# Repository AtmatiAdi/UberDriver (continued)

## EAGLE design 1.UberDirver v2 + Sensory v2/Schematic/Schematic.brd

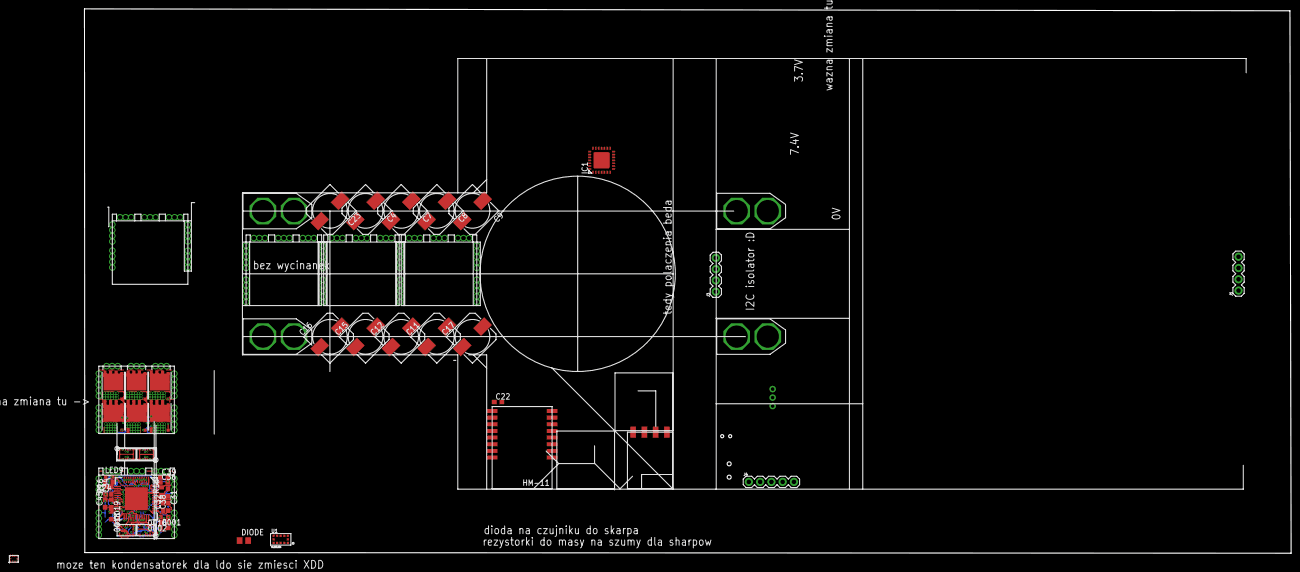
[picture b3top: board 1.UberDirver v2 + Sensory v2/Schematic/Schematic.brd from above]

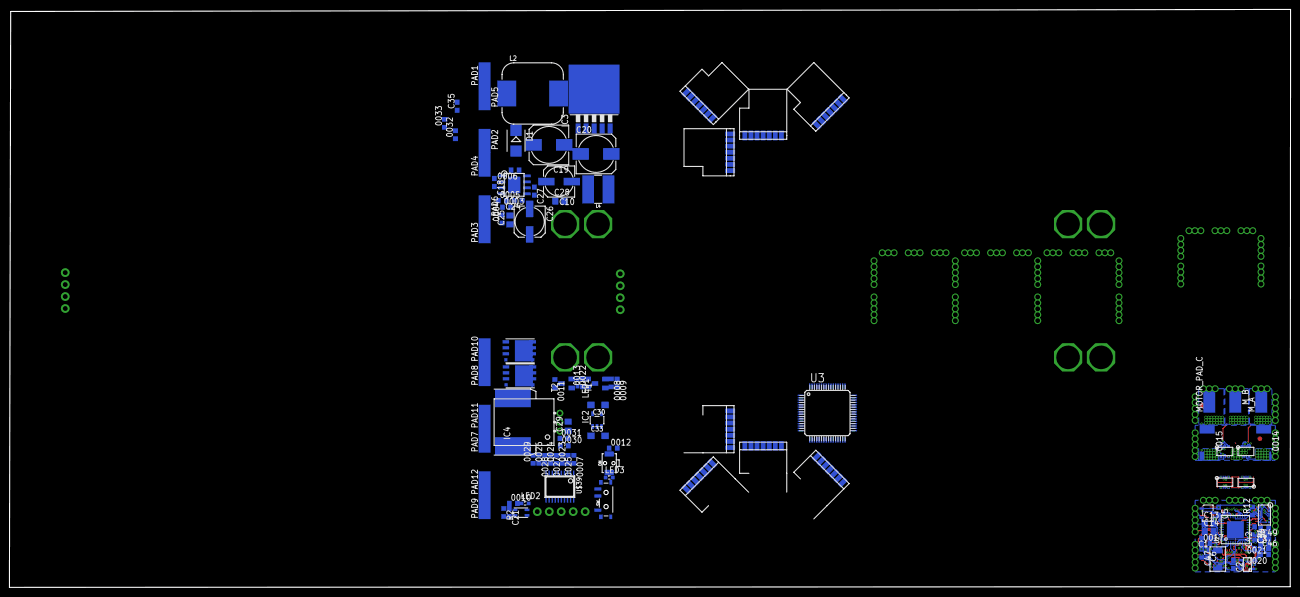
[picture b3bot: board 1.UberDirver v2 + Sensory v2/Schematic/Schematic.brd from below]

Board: 4 copper layers, 271.8 x 122.6 mm, 159 parts (108 on the bottom side), 137 nets.

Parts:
0001, 0016, 0018, 0020: 34.8kR; R0603
0002, 0017, 0019, 0021: 4.99kR; R0603
0003, 0010, 0012, 0013, 0030, 0031: 10k; R0603
0004: 26.1k; R0603
0005: 6.8k; R0603
0006, 0007, 0008, 0011, 0022, 0023, 0025, 0027, 0028: 100k; R0603
0009: 1k; R0603
0014, 0015: 5mohm; R2512
0024: 300k; R0603
0026: 500k; R0603
0029: 700k; R0603
0032, 0033: ?; R0603
C1, C2: 22pF; C0603
C3, C5, C22, C27: 100nF; C0603
C4, C7, C8, C9, C11, C12, C15, C16, C17, C19, C20, C23: 153CLV-0810
C6, C45, C46, C47, C49: 0.1uf; C0603
C10, C26: 10uF; 153CLV-0605
C13, C14: 4.7uF; C0805
C18, C21: 10nF; C0603
C24: 3.9nF; C0603
C25: 22uF; C0805
C28, C29: 10uF; C0805
C30: 10uF/10V; SMC_A
C31, C32: 0.047uF; C0603
C33: 10uf/10V; SMC_A
C34, C36, C38, C39: 1uF; C0603
C35: C0603
C42, C44: 1000pF; C0603
D1: SMB
DIODE: R0805
IC1: MCP23017ML; QFN28-ML_6X6MM
IC2: TPS70933DBV; SOT23-5
IC3: LM2596S; TO263-5
IC4: ACS758ECB-200B-PFF-T; CB-PFF
J1, J3: 1X04
J4: 1X05
L2: CDRH127/LD
L4: 100; SRN6045
LED1, LED2, LED3, LED9: Red; SML0603
MOTOR_PAD_C: SMD2,54-5,08
M_A: SMD2,54-5,08
M_B: SMD2,54-5,08
ON: Button; TACTILE_SWITCH_SMD_RIGHT_ANGLE
PAD1, PAD2, PAD3, PAD4, PAD5, PAD6, PAD7, PAD8, PAD9, PAD10, PAD11, PAD12: SMD2,54-5,08
R1: 180nH; R0603
R2: 100k; R0603
R12, R24: 10k; R0603
R13: 100R; R0603
R16: 100K; R0603
SW: SWITCH_SPST_SMD_A
T1, T2: SOT23-BEC
U1: VL53L0X; LGA12_ST
U2: STM32F10XTXU6HS; VFQFPN36-HS
U3: STM32F10XRXT6; TQFP64
U$1, U$2, U$4, U$5, U$9: MOLEG_REC_8X0.4MM; REC
U$3, U$6, U$7, U$8: MOLEX_PLUG_8X0.4MM; PLUG
U$10: OSC_8MHZ; SMD_MINI
U$11: TLV760XX; SOT-23-3
U$12, U$13, U$22, U$23, U$24, U$25, U$26, U$28: CSD17573Q5B; Q5B
U$14, U$15, U$16, U$18: TOF+SHARP; TOF+SHARP_V1
U$17, U$36, U$37, U$38: XT60
U$19, U$20, U$27, U$29: TOF-SHARP; TOF+SHARP_V2
U$21: DRV8305; S-PQFP-G48
U$30: SUPER_DUPER_GUZICZEK
U$31: TPD4E001; SOT-23
U$32: IR_SW
U$33: TLA2024; X2QFN
U$34: HM-11
U$35: MP2307; SOIC8N
U$39: STM32F030F4; TSSOP20

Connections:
3.7V: 0023.2, PAD9.1, PAD12.1
3V3: 0004.1, C22.2, C25.1, C26.+, J1.3, L4.2, U$32.VCC, U$34.VCC
3V3_L0: 0012.1, C33.+, IC2.5, J4.1, R2.1, U$39.5, U$39.16
5V: 0032.1, C20.+, C29.1, C35.2, IC4.1, J1.4, L2.2, U$14.5V, U$15.5V, U$16.5V, U$18.5V, U$19.5V, U$20.5V, U$27.5V, U$29.5V
7.4V+: 0024.2, C30.+, IC2.1, IC4.IP-, PAD7.1, PAD11.1
7.4V-: IC4.IP+, PAD3.1, PAD6.1
11.1V: 0026.2, PAD1.1, PAD5.1
14.8V: 0029.2, PAD2.1, PAD4.1
+3V3: C5.1, C39.1, C49.1, R1.1, R12.2, R16.1, U2.1, U2.19, U2.27, U$11.1, U$31.5
A3.7: 0007.2, 0023.1, U$39.6
A7.4: 0024.1, 0025.2, U$39.7
A11.1: 0026.1, 0027.2, U$39.8
A14.8: 0028.2, 0029.1, U$39.9
ACURR: 0030.1, 0031.1, U$39.10
BAT-: 0007.1, 0008.1, 0010.1, 0011.2, 0025.1, 0027.1, 0028.1, 0030.2, C21.1, C30.-, C33.-, IC2.2, J4.3, LED3.C, PAD8.1, PAD10.1, T1.E, U$12.S1, U$12.S2, U$12.S3, U$13.S1, U$13.S2, U$13.S3, U$30.T1, U$30.T2, U$39.1, U$39.15
BS: C18.1, U$35.1
BUTTON_L0: LED3.A, ON.1, U$39.13
COMP: C24.1, U$35.6
CURR: 0031.2, IC4.3
EN: 0006.1, U$35.7
ENGATE: U2.24, U$21.1-EN_GATE
FB: 0003.2, 0004.2, U$35.5
GH_ABOT_3: U$9.POWER_2, U$21.36-GH_A
GH_ATOP_2: U$3.POWER_1, U$24.G
GH_BBOT_3: U$4.POWER_4, U$21.29-GH_B
GH_BTOP_2: U$6.POWER_2, U$22.G
GH_CBOT_3: U$4.POWER_3, U$21.28_GH_C
GH_CTOP_1: U$6.POWER_1, U$26.G
GL_ABOT_3: U$9.POWER_3, U$21.33-GL_A
GL_ATOP_2: U$3.POWER_4, U$25.G
GL_BBOT_3: U$4.POWER_2, U$21.32-GL_B
GL_BTOP_2: U$6.POWER_4, U$23.G
GL_CBOT_3: U$4.POWER_1, U$21.25-GL_C
GL_CTOP_1: U$6.POWER_3, U$28.G
GND: 0002.1, 0003.1, 0005.1, 0014.1, 0015.1, 0017.1, 0019.1, 0021.1, 0033.2, C1.2, C2.1, C3.1, C4.-, C5.2, C6.2, C7.-, C8.-, C9.-, C10.-, C11.-, C12.-, C13.2, C15.-, C16.-, C17.-, C19.-, C20.-, C22.1, C23.-, C25.2, C26.-, C27.2, C28.2, C29.2, C34.2, C36.2, C38.2, C39.2, C45.2, C46.2, C47.2, C49.2, D1.A, IC3.3, IC4.2, LED1.C, R24.1, U1.3, U1.4, U1.6, U1.12, U2.5, U2.18, U2.26, U2.35, U2.36, U$1.PAD_1, U$1.PAD_2, U$1.PAD_3, U$1.PAD_4, U$2.PAD_1, U$2.PAD_2, U$2.PAD_3, U$2.PAD_4, U$2.POWER_1, U$3.POWER_3, U$3.SIGNAL_3, U$4.PAD_1, U$4.PAD_2, U$4.PAD_3, U$4.PAD_4, U$5.PAD_1, U$5.PAD_2, U$5.PAD_3, U$5.PAD_4, U$5.POWER_4, U$8.POWER_2, U$9.PAD_1, U$9.PAD_2, U$9.PAD_3, U$9.PAD_4, U$9.POWER_4, U$11.3, U$12.D1, U$12.D2, U$12.D3, U$12.D4, U$12.D5, U$13.D1, U$13.D2, U$13.D3, U$13.D4, U$13.D5, U$14.GND\, U$15.GND\, U$16.GND\, U$17.-, U$18.GND\, U$19.GND\, U$20.GND\, U$21.9-NSCS, U$21.14-GND1, U$21.21-SN2, U$21.22-SP2, U$21.45-GND2, U$21.POWERPAD, U$23.S1, U$23.S2, U$23.S3, U$27.GND\, U$29.GND\, U$31.2, U$32.GND, U$34.GND, U$35.4, U$35.PAD, U$36.-, U$37.-, U$38.-
INH_A: U2.29, U$21.2-INHA
INH_B: U2.13, U$21.4-INHB
INH_C: U2.21, U$21.6-INHC
INL_A: U2.9, U$21.3-INLA
INL_B: U2.14, U$21.5-INLB
INL_C: U2.20, U$21.7-INLC
INPUT: U2.15, U$2.POWER_3
KILL: IC1.22, U$32.KILL
LED: LED9.A, U2.22, U$2.POWER_4
LED_L0: LED2.A, U$39.12
MOSFET: 0009.2, U$39.14
unnamed: 0032.2, 0033.1, C35.1, IC3.4
unnamed: U$5.POWER_3, U$8.POWER_1
unnamed: U$5.SIGNAL_3, U$8.SIGNAL_1
unnamed: U$5.SIGNAL_4, U$8.SIGNAL_2
unnamed: 0008.2, 0009.1, T1.B
unnamed: U$1.POWER_3, U$7.POWER_1
unnamed: U$1.SIGNAL_3, U$7.SIGNAL_1
unnamed: U$1.SIGNAL_4, U$7.SIGNAL_2
unnamed: C36.1, U$21.46-DVDD
unnamed: U$1.POWER_4, U$7.POWER_2
unnamed: C34.1, U$21.15-AVDD
unnamed: C38.1, U$21.37-VCP_LSD
unnamed: C31.2, U$21.42-CP1L
unnamed: U$5.POWER_1, U$8.POWER_3
unnamed: C31.1, U$21.43-CP1H
unnamed: U$5.SIGNAL_1, U$8.SIGNAL_3
unnamed: U$5.SIGNAL_2, U$8.SIGNAL_4
unnamed: U$5.POWER_2, U$8.POWER_4
unnamed: C32.2, U$21.40-CP2L
unnamed: C32.1, U$21.39-CP2H
unnamed: R13.1, U$21.44-VDRAIN
unnamed: C14.2, U$21.38-VCPH
unnamed: C1.1, U2.2, U$10.2
unnamed: U$1.POWER_1, U$7.POWER_3
unnamed: U$1.SIGNAL_1, U$7.SIGNAL_3
unnamed: U$1.SIGNAL_2, U$7.SIGNAL_4
unnamed: U$1.POWER_2, U$7.POWER_4
unnamed: 0022.1, T1.C, T2.B
unnamed: 0005.2, C24.2
unnamed: C3.2, R1.2, U2.6
unnamed: 0010.2, LED2.C
unnamed: C2.2, U2.3, U$10.1
unnamed: 0012.2, ON.2
unnamed: LED9.C, R24.2
unnamed: 0013.1, LED1.A
unnamed: 0011.1, T2.C, U$12.G
NFAULT: R12.1, U2.23, U$21.8-NFAULT
NRST: R16.2, U2.4, U$2.POWER_2
NRST_L0: C21.2, J4.5, R2.2, U$30.T3, U$30.T4, U$39.4
OUT: D1.C, IC3.2, L2.1
SAFE_SW: SW.1, T2.E
SCL: U2.33, U$2.SIGNAL_3
SCLK: U2.30, U$21.12-SCLK
SCL_L: U3.58, U$14.SCL, U$15.SCL, U$16.SCL, U$18.SCL
SCL_L0: J1.1, U$39.17
SCL_R: U3.29, U$19.SCL, U$20.SCL, U$27.SCL, U$29.SCL
SDA: U2.34, U$2.SIGNAL_4
SDA_L: U3.59, U$14.SDA, U$15.SDA, U$16.SDA, U$18.SDA
SDA_L0: J1.2, U$39.18
SDA_R: U3.30, U$19.SDA, U$20.SDA, U$27.SDA, U$29.SDA
SDI: U2.32, U$21.10-SDI
SDO: U2.31, U$21.11-SDO
SHARP_1: IC1.17, U$14.SHARP
SHARP_2: IC1.18, U$15.SHARP
SHARP_3: IC1.19, U$16.SHARP
SHARP_4: IC1.20, U$18.SHARP
SH_ABOT_3: 0018.2, U$9.SIGNAL_1, U$21.35-SH_A
SH_ATOP_2: M_A.1, U$3.SIGNAL_2, U$24.S1, U$24.S2, U$24.S3, U$25.D1, U$25.D2, U$25.D3, U$25.D4, U$25.D5
SH_BBOT_3: 0020.2, U$9.SIGNAL_2, U$21.30-SH_B
SH_BTOP_2: M_B.1, U$3.SIGNAL_1, U$22.S1, U$22.S2, U$22.S3, U$23.D1, U$23.D2, U$23.D3, U$23.D4, U$23.D5
SH_CBOT_3: 0016.2, U$4.SIGNAL_4, U$21.27-SH_C
SH_CTOP_1: MOTOR_PAD_C.1, U$6.SIGNAL_2, U$26.S1, U$26.S2, U$26.S3, U$28.D1, U$28.D2, U$28.D3, U$28.D4, U$28.D5
SL_ABOT_3: C42.1, U$9.SIGNAL_3, U$21.23-SN1, U$21.34-SL_A
SL_ATOP_2: 0014.2, U$3.SIGNAL_4, U$25.S1, U$25.S2, U$25.S3
SL_BOT_3: U$9.SIGNAL_4, U$21.31-SL_B
SL_CTOP_1: 0015.2, U$6.SIGNAL_3, U$28.S1, U$28.S2, U$28.S3
SL_C_2<2: C44.1, U$4.SIGNAL_1, U$21.19-SN3, U$21.26-SL_C
SO1: U2.16, U$21.16-SO1
SO3: U2.12, U$21.18-SO3
SP_ABOT_3: C42.2, U$4.SIGNAL_2, U$21.24-SP1
SP_CBOT_3: C44.2, U$4.SIGNAL_3, U$21.20-SP3
SS: C27.1, U$35.8
START: IC1.21, U$32.START
SW: C18.2, L4.1, U$35.3
SWCLK: U2.28, U$2.SIGNAL_2
SWCLK_L0: J4.2, U$39.20
SWDIO: U2.25, U$2.SIGNAL_1
SWDIO_L0: J4.4, U$39.19
VA: 0018.1, 0019.2, C45.1, U2.7, U$31.1
VB: 0020.1, 0021.2, C46.1, U2.8, U$31.3
VC: 0016.1, 0017.2, C47.1, U2.10, U$31.4
VIN: 0006.2, 0013.2, 0022.2, C4.+, C7.+, C8.+, C9.+, C10.+, C11.+, C12.+, C15.+, C16.+, C17.+, C23.+, C28.1, SW.2, U$17.+, U$35.2, U$36.+, U$37.+, U$38.+
VIN1: C19.+, IC3.1
VMOTOR: 0001.2, C13.1, C14.1, R13.2, U$9.POWER_1, U$11.2, U$21.41-PVDD
VMOTOR_TOP: U$3.POWER_2, U$22.D1, U$22.D2, U$22.D3, U$22.D4, U$22.D5, U$24.D1, U$24.D2, U$24.D3, U$24.D4, U$24.D5, U$26.D1, U$26.D2, U$26.D3, U$26.D4, U$26.D5
VV: 0001.1, 0002.2, C6.1, U2.11, U$31.6
WAKE: U2.17, U$21.47-WAKE
XSHUT_1: IC1.25, U$14.XSHUT
XSHUT_2: IC1.26, U$15.XSHUT
XSHUT_3: IC1.27, U$16.XSHUT
XSHUT_4: IC1.28, U$18.XSHUT

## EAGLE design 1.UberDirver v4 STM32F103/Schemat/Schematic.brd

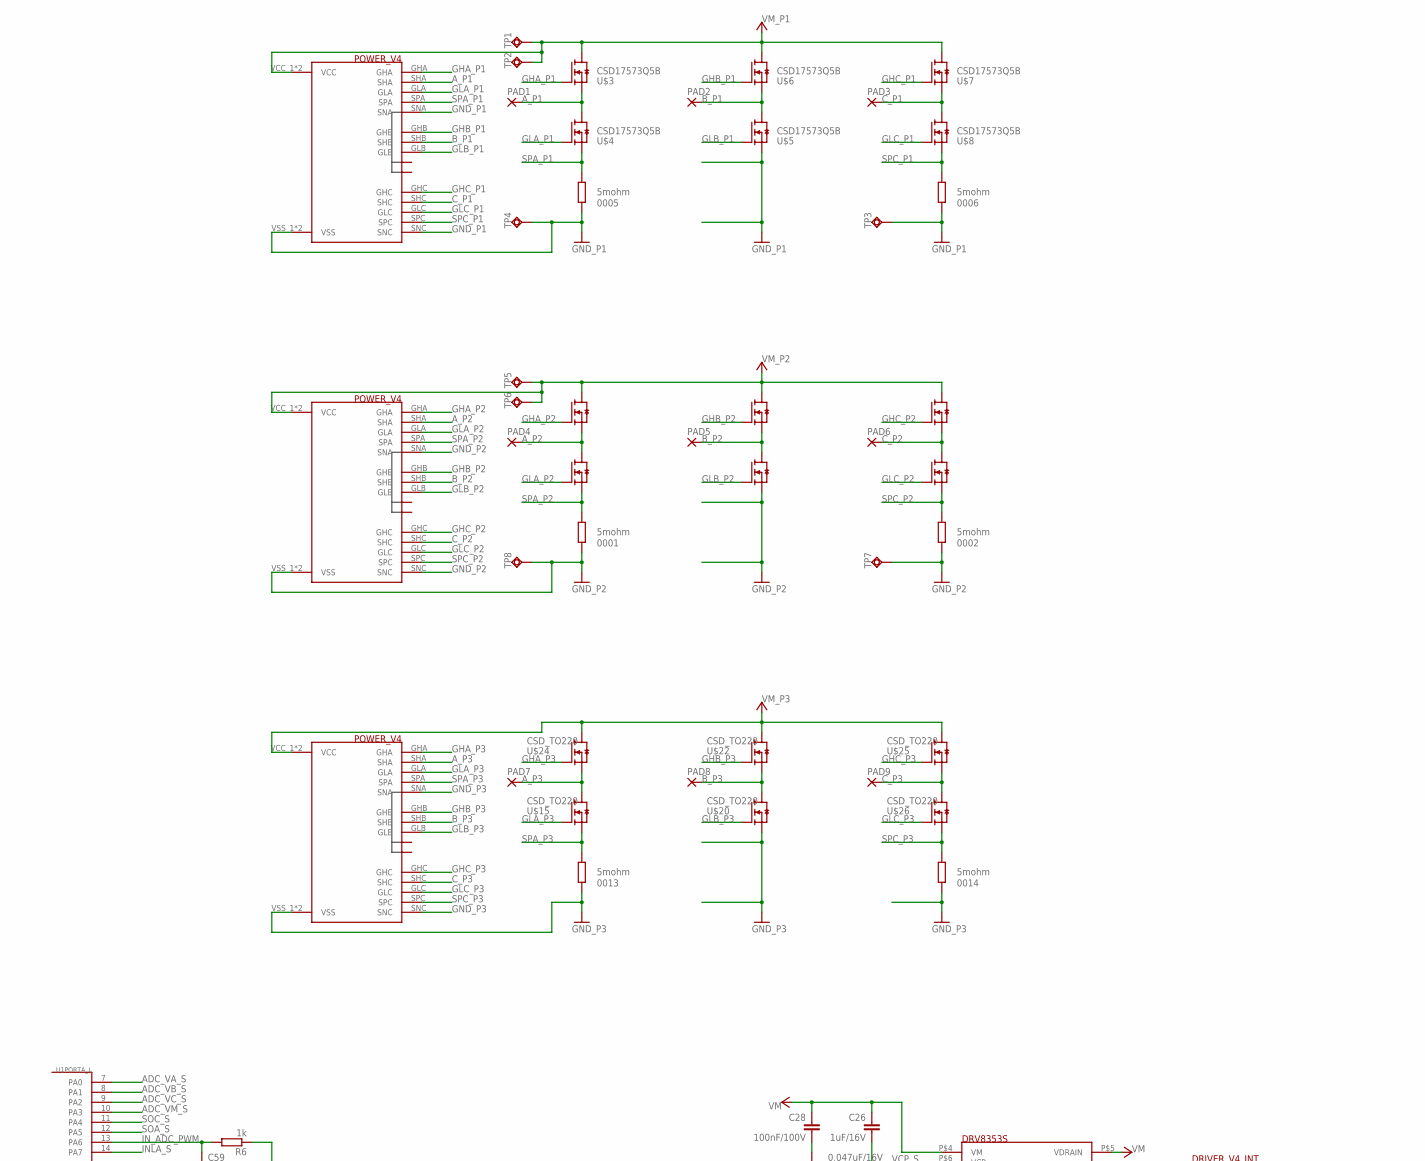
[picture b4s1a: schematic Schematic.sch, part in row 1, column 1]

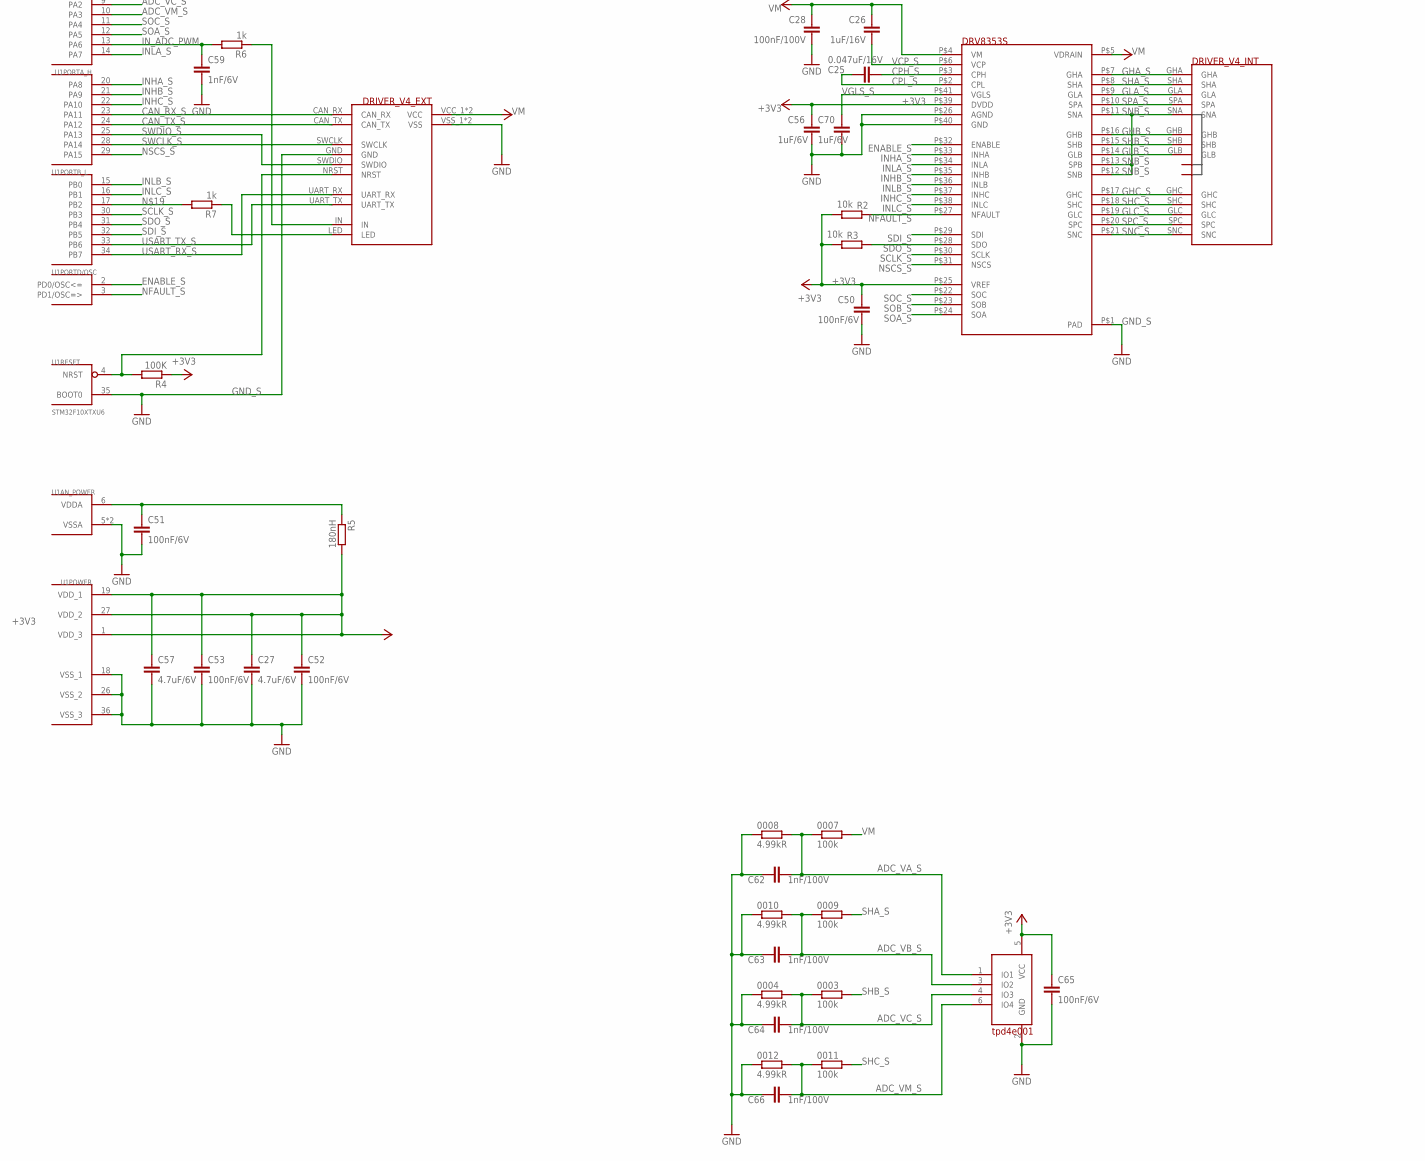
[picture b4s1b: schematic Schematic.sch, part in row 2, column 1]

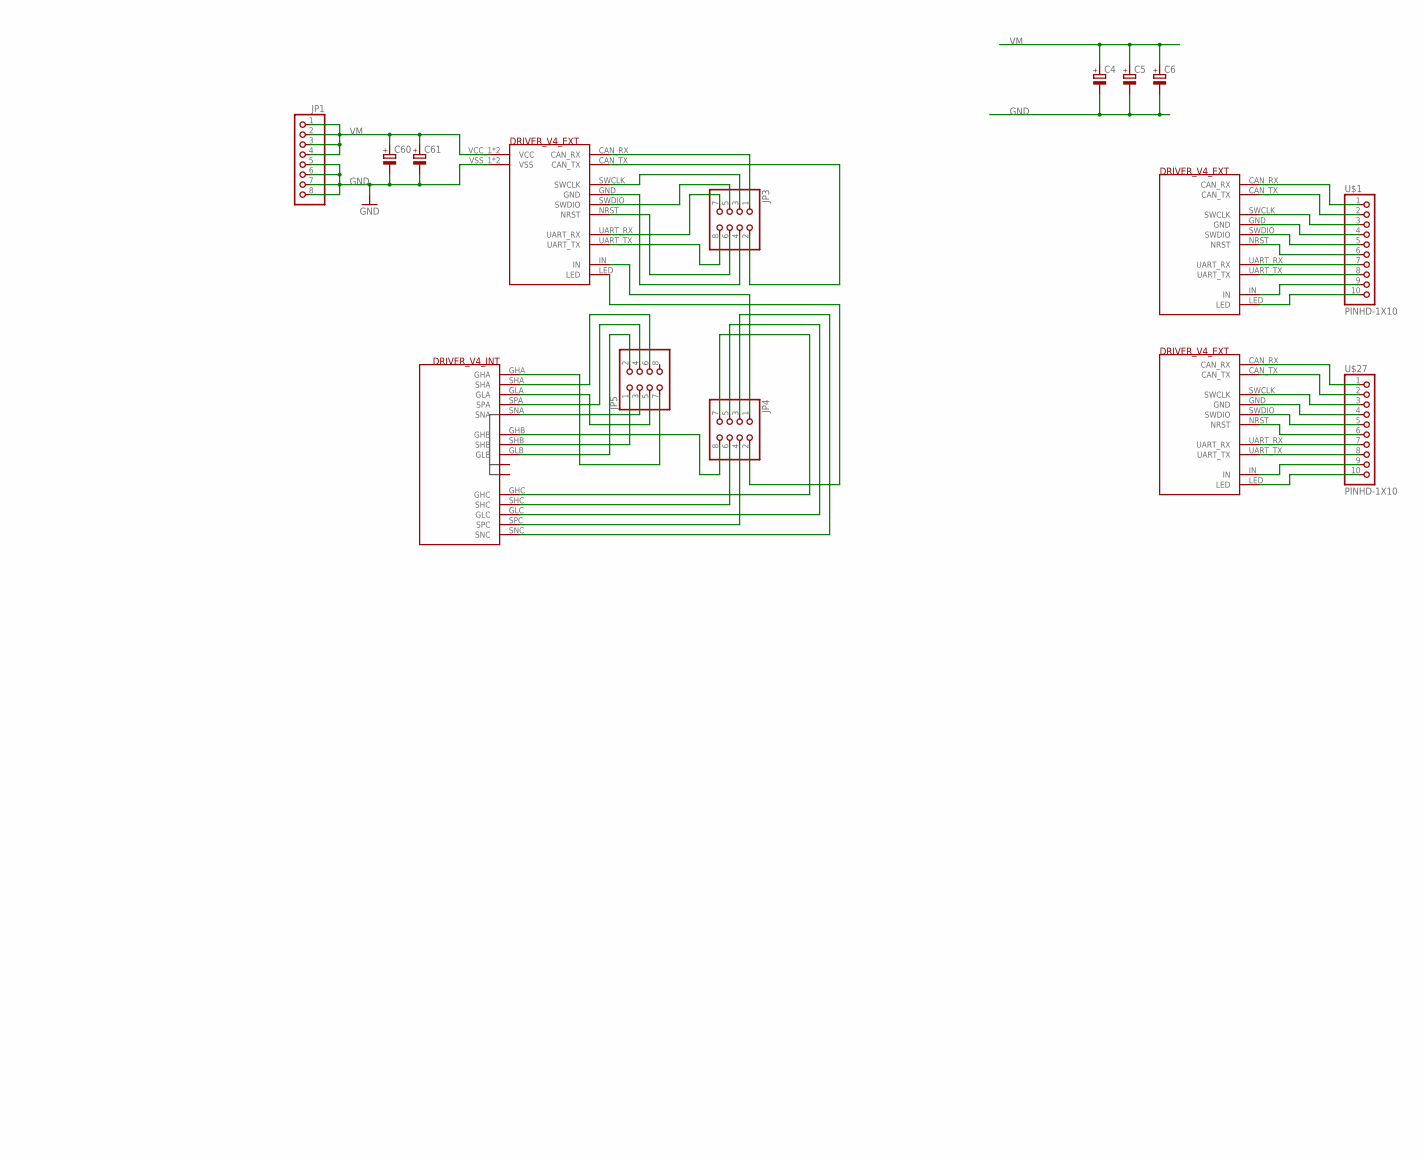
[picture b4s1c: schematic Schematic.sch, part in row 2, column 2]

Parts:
0001, 0002, 0005, 0006, 0013, 0014: 5mohm; R2512
0003, 0007, 0009, 0011: 100k; R0402
0004, 0008, 0010, 0012: 4.99kR; R0402
C4, C5, C6, C60, C61: CPOL-EUE3.5-10; E3,5-10
C25: 0.047uF/16V; R0402
C26: 1uF/16V; R0402
C27, C57: 4.7uF/6V; R0402
C28: 100nF/100V; R0402
C50, C51, C52, C53, C65: 100nF/6V; R0402
C56, C70: 1uF/6V; R0402
C59: 1nF/6V; R0402
C62, C63, C64, C66: 1nF/100V; R0402
JP1: PINHD-1X8BIG; 1X08-BIG
JP3, JP4, JP5: PINHD-2X4; 2X04
PAD1, PAD2, PAD3, PAD4, PAD5, PAD6, PAD7, PAD8, PAD9: SMD5; SMD2,54-5,08
R2, R3: 10k; R0402
R4: 100K; R0402
R5: 180nH; R0402
R6, R7: 1k; R0402
TP1, TP2, TP3, TP4, TP5, TP6, TP7, TP8: TPSQTP20SQ; TP20SQ
U1: STM32F10XTXU6; VFQFPN36
U$1, U$27: PINHD-1X10; 1X10-BIG
U$2, U$23: UBER_V4_DEVICE; DRIVER_V4_DEVICE
U$3, U$4, U$5, U$6, U$7, U$8: CSD17573Q5B; Q5B
U$9: TPD4E001; SOT-23
U$10, U$11, U$12, U$13, U$14, U$18: INFINEON_007N06N; PG-HSOF-8
U$15, U$20, U$22, U$24, U$25, U$26: CSD_TO220; TO220
U$16: DRV8353S; 40-PIN_WQFN
U$17: UBER_V4_MASTER; DRIVER_V4_MASTER
U$19, U$29, U$38: UBER_V4_POWER; DRIVER_V4_POWER
U$21: UBER_V4&P1; DRIVER_V4&P1

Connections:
+3V3: C27.1, C50.1, C52.1, C53.1, C56.1, C57.1, C65.1, R2.1, R3.1, R4.1, R5.2, U1.1 (VDD_3), U1.19 (VDD_1), U1.27 (VDD_2), U$9.5 (VCC), U$16.P$25 (VREF), U$16.P$39 (DVDD)
ADC_VA_S: 0007.1, 0008.2, C62.1, U1.7 (PA0), U$9.1 (IO1)
ADC_VB_S: 0009.1, 0010.2, C63.1, U1.8 (PA1), U$9.3 (IO2)
ADC_VC_S: 0003.1, 0004.2, C64.1, U1.9 (PA2), U$9.4 (IO3)
ADC_VM_S: 0011.1, 0012.2, C66.1, U1.10 (PA3), U$9.6 (IO4)
A_P1: PAD1.1, U$3.S, U$4.D1 (D), U$38.SHA
A_P2: PAD4.1, U$10.D, U$18.S, U$19.SHA
A_P3: PAD7.1, U$15.D, U$24.S, U$29.SHA
B_P1: PAD2.1, U$5.D1 (D), U$6.S, U$38.SHB
B_P2: PAD5.1, U$11.S, U$12.D, U$19.SHB
B_P3: PAD8.1, U$20.D, U$22.S, U$29.SHB
CAN_RX_S: U1.23 (PA11), U$17.CAN_RX
CAN_TX_S: U1.24 (PA12), U$17.CAN_TX
CPH_S: C25.1, U$16.P$3 (CPH)
CPL_S: C25.2, U$16.P$2 (CPL)
C_P1: PAD3.1, U$7.S, U$8.D1 (D), U$38.SHC
C_P2: PAD6.1, U$13.S, U$14.D, U$19.SHC
C_P3: PAD9.1, U$25.S, U$26.D, U$29.SHC
ENABLE_S: U1.2 (PD0/OSC<=), U$16.P$32 (ENABLE)
GHA_P1: U$3.G, U$38.GHA
GHA_P2: U$18.G, U$19.GHA
GHA_P3: U$24.G, U$29.GHA
GHA_S: U$16.P$7 (GHA), U$17.GHA
GHB_P1: U$6.G, U$38.GHB
GHB_P2: U$11.G, U$19.GHB
GHB_P3: U$22.G, U$29.GHB
GHB_S: U$16.P$16 (GHB), U$17.GHB
GHC_P1: U$7.G, U$38.GHC
GHC_P2: U$13.G, U$19.GHC
GHC_P3: U$25.G, U$29.GHC
GHC_S: U$16.P$17 (GHC), U$17.GHC
GLA_P1: U$4.G, U$38.GLA
GLA_P2: U$10.G, U$19.GLA
GLA_P3: U$15.G, U$29.GLA
GLA_S: U$16.P$9 (GLA), U$17.GLA
GLB_P1: U$5.G, U$38.GLB
GLB_P2: U$12.G, U$19.GLB
GLB_P3: U$20.G, U$29.GLB
GLB_S: U$16.P$14 (GLB), U$17.GLB
GLC_P1: U$8.G, U$38.GLC
GLC_P2: U$14.G, U$19.GLC
GLC_P3: U$26.G, U$29.GLC
GLC_S: U$16.P$19 (GLC), U$17.GLC
GND: C4.-, C5.-, C6.-, C60.-, C61.-, JP1.5, JP1.6, JP1.7, JP1.8, U$21.VSS_1 (VSS), U$21.VSS_2 (VSS)
GND_P1: 0005.1, 0006.1, TP3.TP, TP4.TP, U$5.S, U$38.SNA, U$38.SNC, U$38.VSS_1 (VSS), U$38.VSS_2 (VSS)
GND_P2: 0001.1, 0002.1, TP7.TP, TP8.TP, U$12.S, U$19.SNA, U$19.SNC, U$19.VSS_1 (VSS), U$19.VSS_2 (VSS)
GND_P3: 0013.1, 0014.1, U$20.S, U$29.SNA, U$29.SNC, U$29.VSS_1 (VSS), U$29.VSS_2 (VSS)
GND_S: 0004.1, 0008.1, 0010.1, 0012.1, C27.2, C28.2, C50.2, C51.2, C52.2, C53.2, C56.2, C57.2, C59.2, C62.2, C63.2, C64.2, C65.2, C66.2, C70.2, U1.5 (VSSA), U1.18 (VSS_1), U1.26 (VSS_2), U1.35 (BOOT0), U1.36 (VSS_3), U1.P$1 (VSSA), U$9.2 (GND), U$16.P$1 (PAD), U$16.P$26 (AGND), U$16.P$40 (GND), U$17.GND, U$17.VSS_1 (VSS), U$17.VSS_2 (VSS)
INHA_S: U1.20 (PA8), U$16.P$33 (INHA)
INHB_S: U1.21 (PA9), U$16.P$35 (INHB)
INHC_S: U1.22 (PA10), U$16.P$37 (INHC)
INLA_S: U1.14 (PA7), U$16.P$34 (INLA)
INLB_S: U1.15 (PB0), U$16.P$36 (INLB)
INLC_S: U1.16 (PB1), U$16.P$38 (INLC)
IN_ADC_PWM: R6.1, U$17.IN
LED_S: R7.1, U$17.LED
unnamed: JP4.3, U$21.SNC
unnamed: JP4.4, U$21.SPC
unnamed: JP4.5, U$21.GLC
unnamed: JP4.6, U$21.SHC
unnamed: JP4.7, U$21.GHC
unnamed: JP4.8, U$21.GHB
unnamed: JP5.1, U$21.SHB
unnamed: JP5.2, U$21.GLB
unnamed: JP5.3, U$21.SNA
unnamed: JP5.4, U$21.SPA
unnamed: JP5.5, U$21.GLA
unnamed: JP5.6, U$21.SHA
unnamed: JP5.7, U$21.GHA
unnamed: JP3.1, U$21.CAN_RX
unnamed: C51.1, R5.1, U1.6 (VDDA)
unnamed: JP3.2, U$21.CAN_TX
unnamed: C59.1, R6.2, U1.13 (PA6)
unnamed: U$1.1, U$2.CAN_RX
unnamed: R7.2, U1.17 (PB2)
unnamed: JP3.3, U$21.SWCLK
unnamed: JP3.4, U$21.GND
unnamed: JP3.5, U$21.SWDIO
unnamed: JP3.6, U$21.NRST
unnamed: U$1.2, U$2.CAN_TX
unnamed: JP3.7, U$21.UART_RX
unnamed: JP3.8, U$21.UART_TX
unnamed: JP4.1, U$21.IN
unnamed: JP4.2, U$21.LED
unnamed: U$1.3, U$2.SWCLK
unnamed: U$1.4, U$2.GND
unnamed: U$1.5, U$2.SWDIO
unnamed: U$1.6, U$2.NRST
unnamed: U$1.7, U$2.UART_RX
unnamed: U$1.8, U$2.UART_TX
unnamed: U$1.9, U$2.IN
unnamed: U$1.10, U$2.LED
unnamed: U$23.CAN_RX, U$27.1
unnamed: U$23.CAN_TX, U$27.2
unnamed: U$23.SWCLK, U$27.3
unnamed: U$23.GND, U$27.4
unnamed: U$23.SWDIO, U$27.5
unnamed: U$23.NRST, U$27.6
unnamed: U$23.UART_RX, U$27.7
unnamed: U$23.UART_TX, U$27.8
unnamed: U$23.IN, U$27.9
unnamed: U$23.LED, U$27.10
NFAULT_S: R2.2, U1.3 (PD1/OSC=>), U$16.P$27 (NFAULT)
NRST_S: R4.2, U1.4 (NRST), U$17.NRST
NSCS_S: U1.29 (PA15), U$16.P$31 (NSCS)
SCLK_S: U1.30 (PB3), U$16.P$30 (SCLK)
SDI_S: U1.32 (PB5), U$16.P$29 (SDI)
SDO_S: R3.2, U1.31 (PB4), U$16.P$28 (SDO)
SHA_S: 0009.2, U$16.P$8 (SHA), U$17.SHA
SHB_S: 0003.2, U$16.P$15 (SHB), U$17.SHB
SHC_S: 0011.2, U$16.P$18 (SHC), U$17.SHC
SNB_S: U$16.P$11 (SNA), U$16.P$12 (SNB), U$16.P$13 (SPB), U$17.SNA
SNC_S: U$16.P$21 (SNC), U$17.SNC
SOA_S: U1.12 (PA5), U$16.P$24 (SOA)
SOB_S: U$16.P$23 (SOB)
SOC_S: U1.11 (PA4), U$16.P$22 (SOC)
SPA_P1: 0005.2, U$4.S, U$38.SPA
SPA_P2: 0001.2, U$10.S, U$19.SPA
SPA_P3: 0013.2, U$15.S, U$29.SPA
SPA_S: U$16.P$10 (SPA), U$17.SPA
SPC_P1: 0006.2, U$8.S, U$38.SPC
SPC_P2: 0002.2, U$14.S, U$19.SPC
SPC_P3: 0014.2, U$26.S, U$29.SPC
SPC_S: U$16.P$20 (SPC), U$17.SPC
SWCLK_S: U1.28 (PA14), U$17.SWCLK
SWDIO_S: U1.25 (PA13), U$17.SWDIO
USART_RX_S: U1.34 (PB7), U$17.UART_RX
USART_TX_S: U1.33 (PB6), U$17.UART_TX
VCP_S: C26.2, U$16.P$6 (VCP)
VGLS_S: C70.1, U$16.P$41 (VGLS)
VM: 0007.2, C4.+, C5.+, C6.+, C26.1, C28.1, C60.+, C61.+, JP1.1, JP1.2, JP1.3, JP1.4, U$16.P$4 (VM), U$16.P$5 (VDRAIN), U$17.VCC_1 (VCC), U$17.VCC_2 (VCC), U$21.VCC_1 (VCC), U$21.VCC_2 (VCC)
VM_P1: TP1.TP, TP2.TP, U$3.D1 (D), U$6.D1 (D), U$7.D1 (D), U$38.VCC_1 (VCC), U$38.VCC_2 (VCC)
VM_P2: TP5.TP, TP6.TP, U$11.D, U$13.D, U$18.D, U$19.VCC_1 (VCC), U$19.VCC_2 (VCC)
VM_P3: U$22.D, U$24.D, U$25.D, U$29.VCC_1 (VCC), U$29.VCC_2 (VCC)

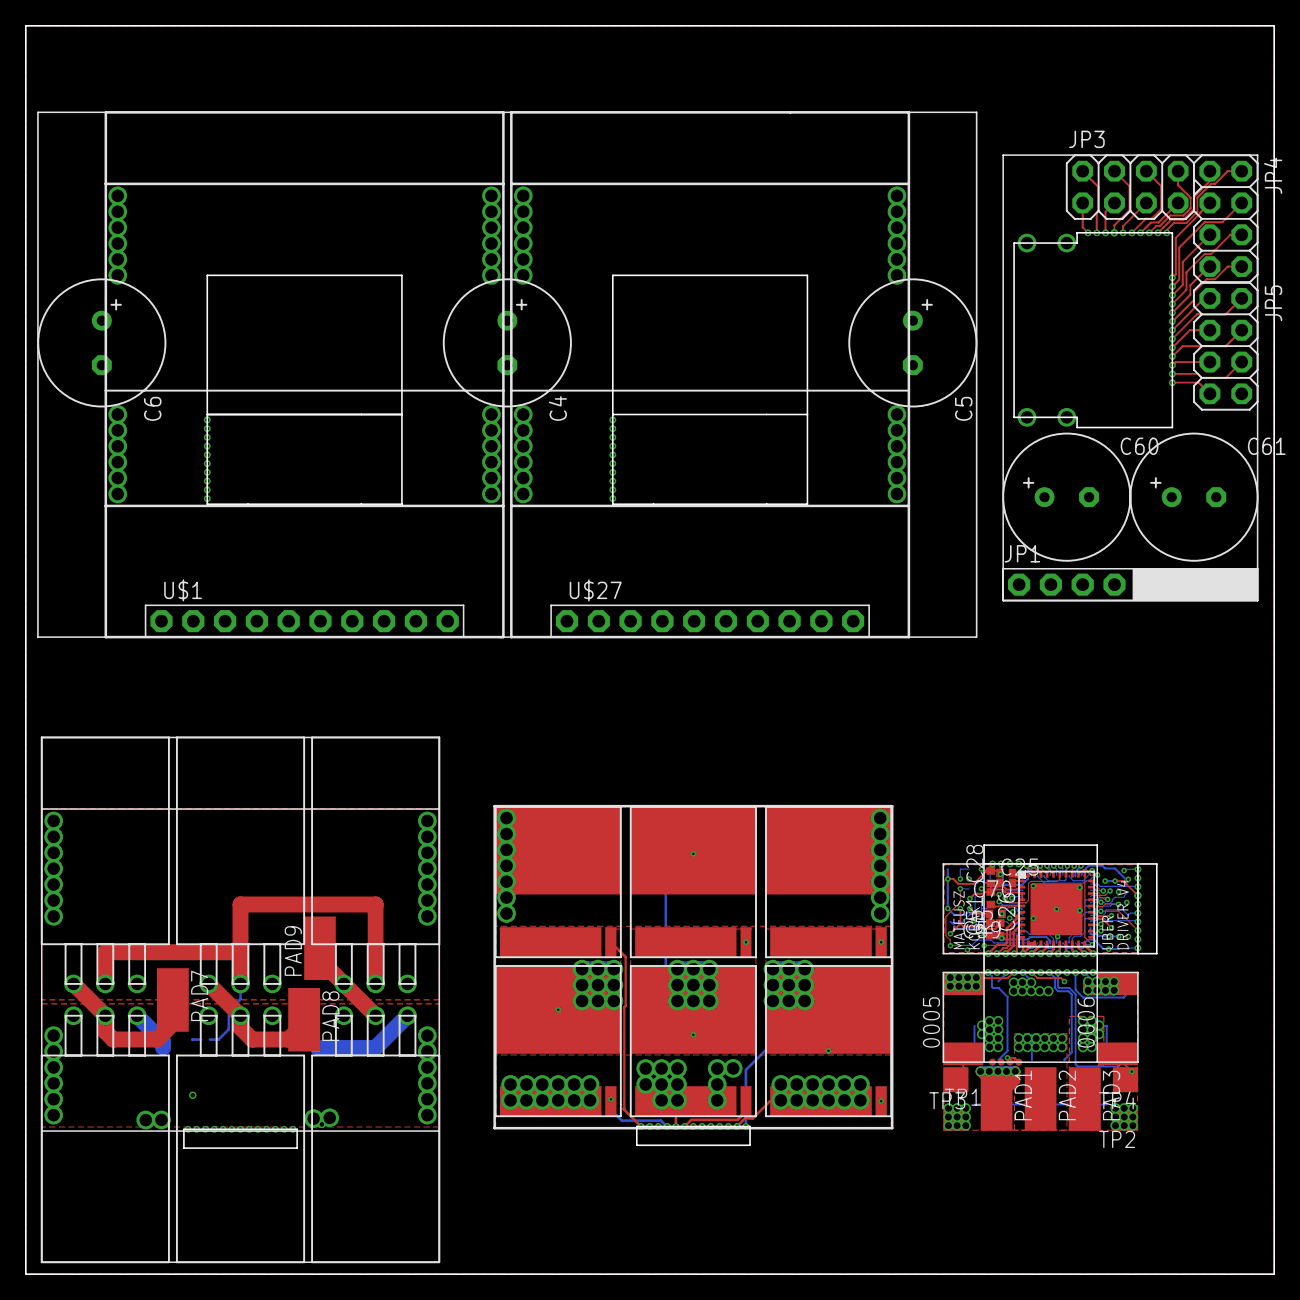
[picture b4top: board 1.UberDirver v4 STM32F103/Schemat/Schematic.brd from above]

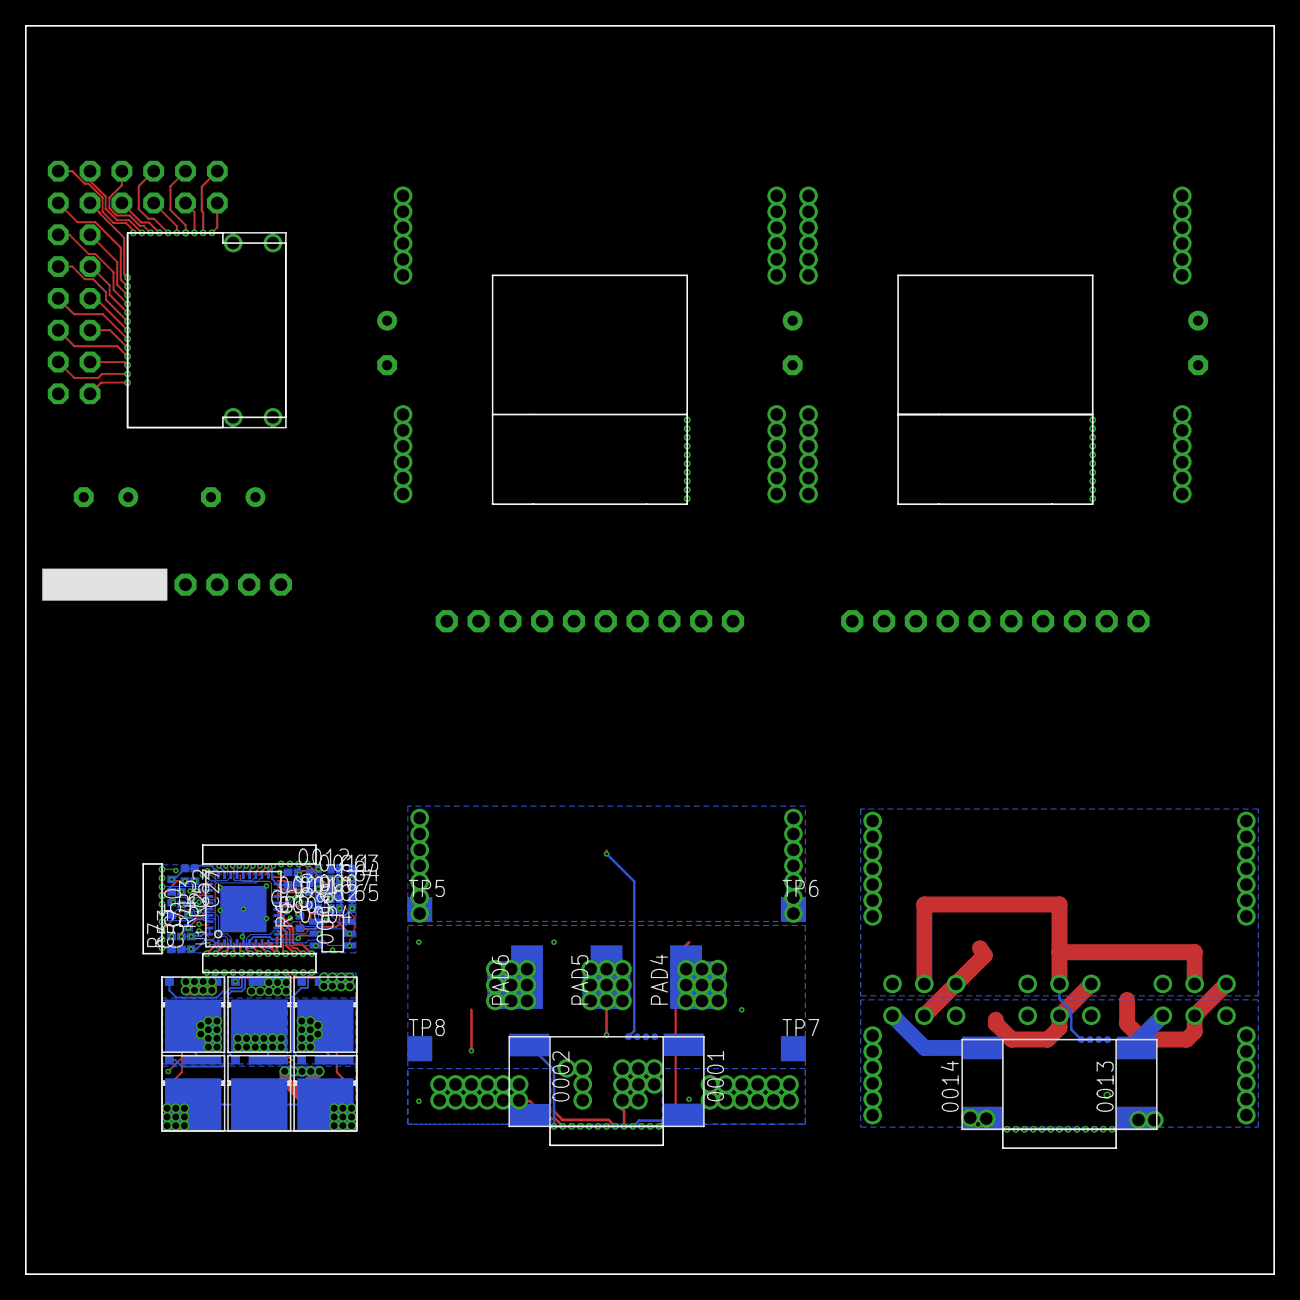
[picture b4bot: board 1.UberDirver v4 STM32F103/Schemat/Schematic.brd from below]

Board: 4 copper layers, 99.7 x 99.7 mm, 93 parts (46 on the bottom side), 133 nets.
